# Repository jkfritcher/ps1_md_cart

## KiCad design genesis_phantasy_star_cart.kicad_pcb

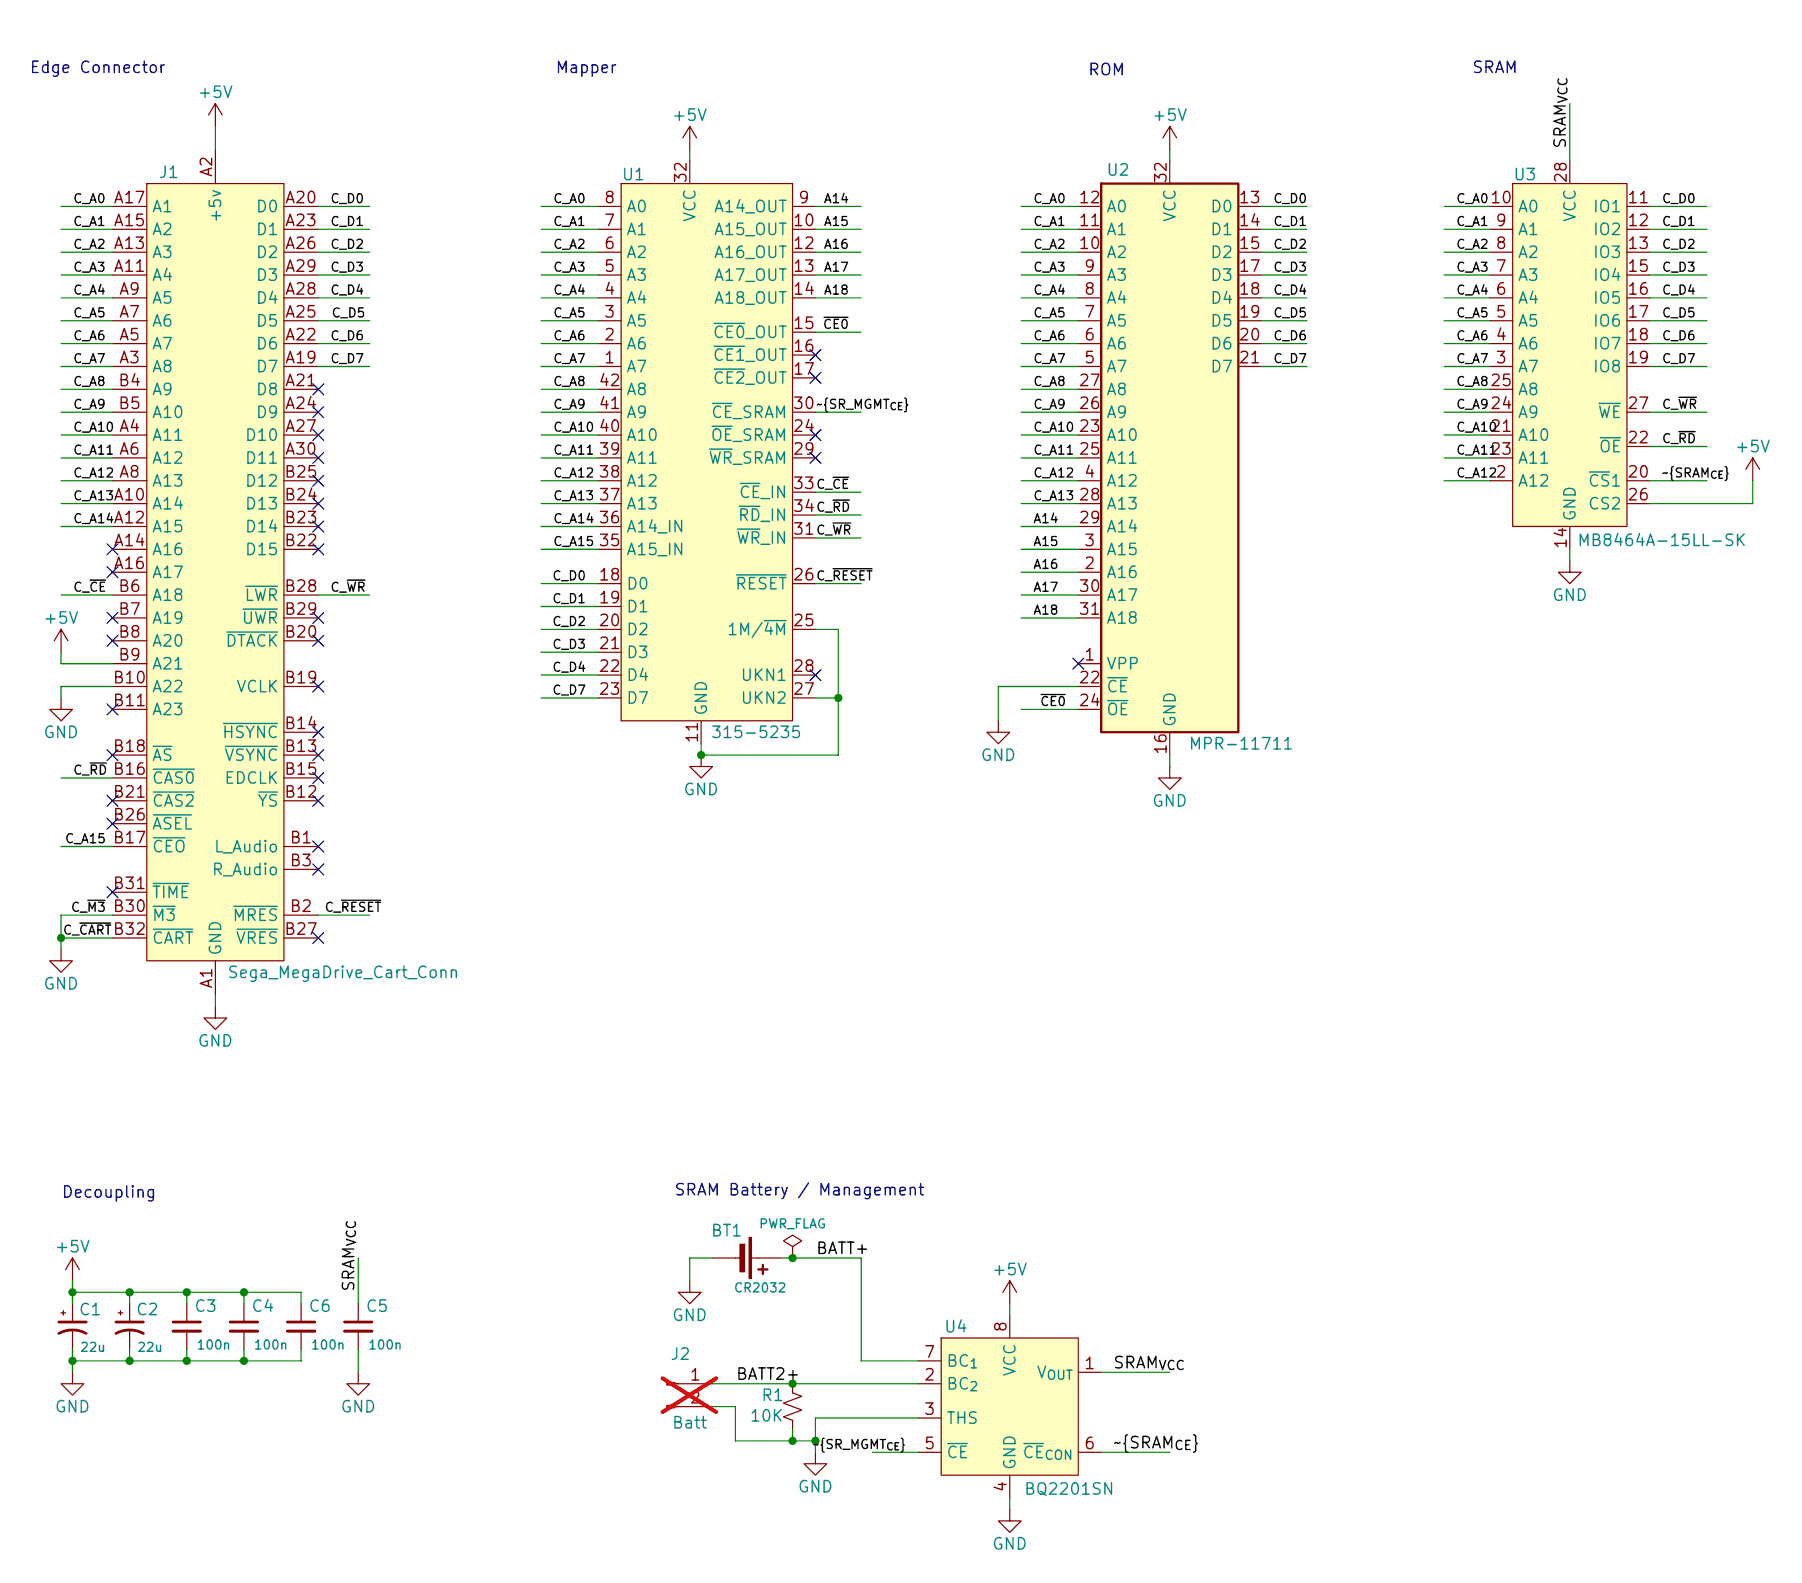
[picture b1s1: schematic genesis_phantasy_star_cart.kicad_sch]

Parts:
BT1: CR2032; CR2032L-F1N
C1, C2: 22u; CP_Elec_4x5.4
C3, C4, C5, C6: 100n; C_0603_1608Metric
J1: Sega_MegaDrive_Cart_Conn; 2x32_P2.54mm_Edge
J2: Batt; PinHeader_1x02_P2.54mm_Vertical; not fitted
R1: 10K; R_0603_1608Metric
U1: 315-5235; SPDIP-42_W15.24mm_P1.78mm
U2: MPR-11711; DIP-32_W15.24mm_LongPads
U3: MB8464A-15LL-SK; DIP-28_W7.62mm_LongPads
U4: BQ2201SN; SOIC-8_3.9x4.9mm_P1.27mm

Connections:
+5V: C1.1, C2.1, C3.1, C4.1, C6.1, J1.A2 (+5v), J1.A31 (+5v), J1.B9 (A21), U1.32 (VCC), U2.32 (VCC), U3.26 (CS2), U4.8 (VCC)
/A14: U1.9 (A14_OUT), U2.29 (A14)
/A15: U1.10 (A15_OUT), U2.3 (A15)
/A16: U1.12 (A16_OUT), U2.2 (A16)
/A17: U1.13 (A17_OUT), U2.30 (A17)
/A18: U1.14 (A18_OUT), U2.31 (A18)
/BATT2+: J2.1, R1.1, U4.2 (BC_{2})
/BATT+: BT1.1 (+), U4.7 (BC_{1})
/C_A0: J1.A17 (A1), U1.8 (A0), U2.12 (A0), U3.10 (A0)
/C_A1: J1.A15 (A2), U1.7 (A1), U2.11 (A1), U3.9 (A1)
/C_A2: J1.A13 (A3), U1.6 (A2), U2.10 (A2), U3.8 (A2)
/C_A3: J1.A11 (A4), U1.5 (A3), U2.9 (A3), U3.7 (A3)
/C_A4: J1.A9 (A5), U1.4 (A4), U2.8 (A4), U3.6 (A4)
/C_A5: J1.A7 (A6), U1.3 (A5), U2.7 (A5), U3.5 (A5)
/C_A6: J1.A5 (A7), U1.2 (A6), U2.6 (A6), U3.4 (A6)
/C_A7: J1.A3 (A8), U1.1 (A7), U2.5 (A7), U3.3 (A7)
/C_A8: J1.B4 (A9), U1.42 (A8), U2.27 (A8), U3.25 (A8)
/C_A9: J1.B5 (A10), U1.41 (A9), U2.26 (A9), U3.24 (A9)
/C_A10: J1.A4 (A11), U1.40 (A10), U2.23 (A10), U3.21 (A10)
/C_A11: J1.A6 (A12), U1.39 (A11), U2.25 (A11), U3.23 (A11)
/C_A12: J1.A8 (A13), U1.38 (A12), U2.4 (A12), U3.2 (A12)
/C_A13: J1.A10 (A14), U1.37 (A13), U2.28 (A13)
/C_A14: J1.A12 (A15), U1.36 (A14_IN)
/C_A15: J1.B17 (~CEO), U1.35 (A15_IN)
/C_D0: J1.A20 (D0), U1.18 (D0), U2.13 (D0), U3.11 (IO1)
/C_D1: J1.A23 (D1), U1.19 (D1), U2.14 (D1), U3.12 (IO2)
/C_D2: J1.A26 (D2), U1.20 (D2), U2.15 (D2), U3.13 (IO3)
/C_D3: J1.A29 (D3), U1.21 (D3), U2.17 (D3), U3.15 (IO4)
/C_D4: J1.A28 (D4), U1.22 (D4), U2.18 (D4), U3.16 (IO5)
/C_D5: J1.A25 (D5), U2.19 (D5), U3.17 (IO6)
/C_D6: J1.A22 (D6), U2.20 (D6), U3.18 (IO7)
/C_D7: J1.A19 (D7), U1.23 (D7), U2.21 (D7), U3.19 (IO8)
/C_~CE: J1.B6 (A18), U1.33 (~CE_IN)
/C_~RD: J1.B16 (~CAS0), U1.34 (~RD_IN), U3.22 (~OE)
/C_~RESET: J1.B2 (~MRES), U1.26 (~RESET)
/C_~WR: J1.B28 (~LWR), U1.31 (~WR_IN), U3.27 (~WE)
/SRAM_{VCC}: C5.1, U3.28 (VCC), U4.1 (V_{OUT})
/~CE0: U1.15 (~CE0_OUT), U2.24 (~OE)
/~SRAM_{CE}: U3.20 (~CS1), U4.6 (~CE_{CON})
/~SR_MGMT_{CE}: U1.30 (~CE_SRAM), U4.5 (~CE)
GND: BT1.2 (-), C1.2, C2.2, C3.2, C4.2, C5.2, C6.2, J1.A1 (GND), J1.A18 (GND), J1.A32 (GND), J1.B10 (A22), J1.B30 (~M3), J1.B32 (~CART), J2.2, R1.2, U1.11 (GND), U1.25 (1M/~4M), U1.27 (UKN2), U2.16 (GND), U2.22 (~CE), U3.14 (GND), U4.3 (THS), U4.4 (GND)

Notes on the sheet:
Decoupling
Mapper
Edge Connector
SRAM
ROM
SRAM Battery / Management

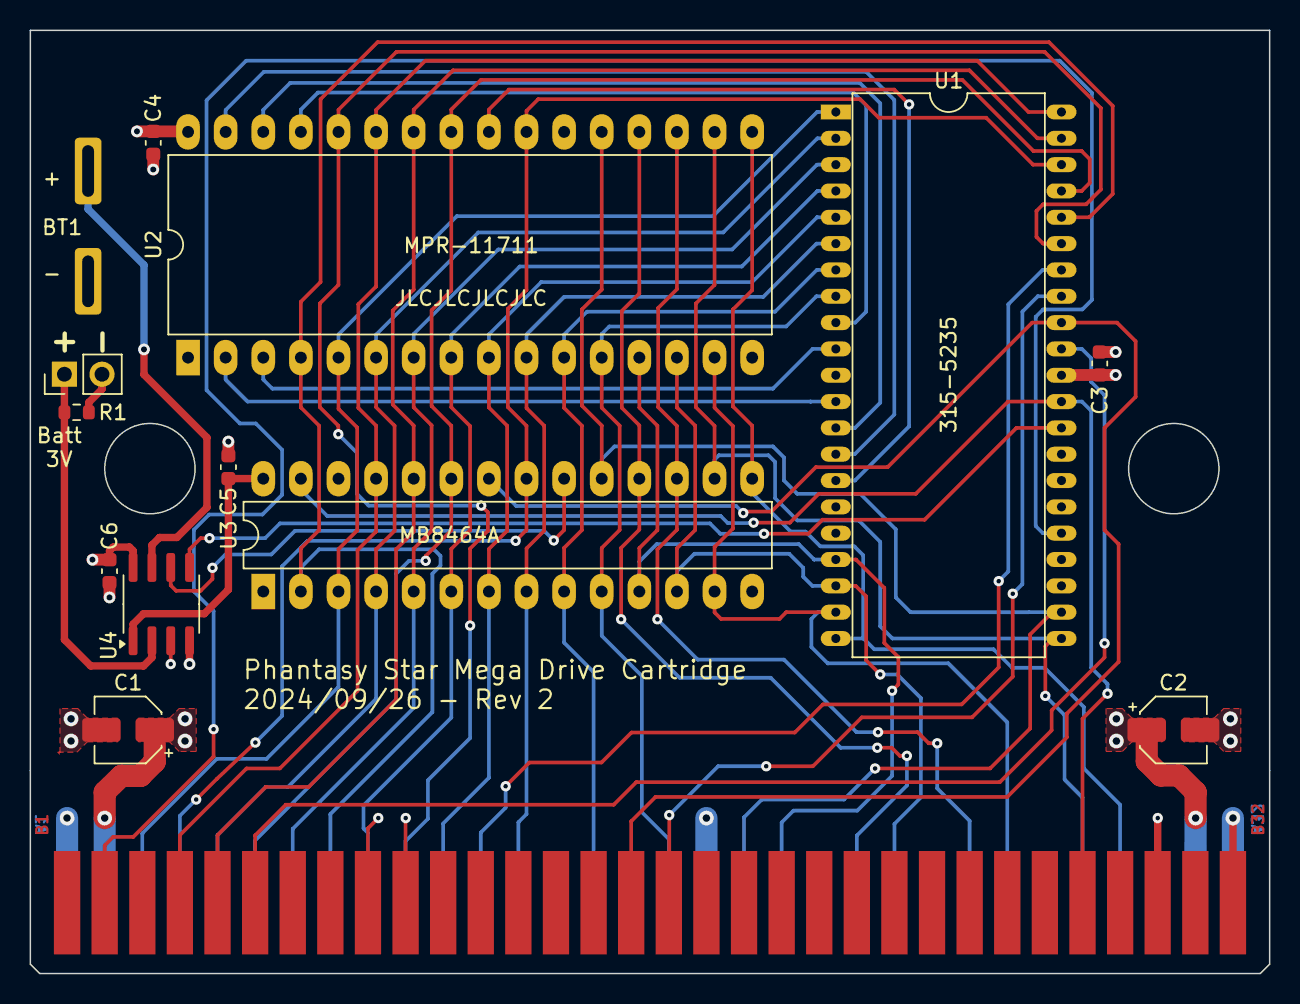
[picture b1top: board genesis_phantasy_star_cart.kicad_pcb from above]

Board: 4 copper layers, 83.7 x 63.7 mm, 14 parts (1 on the bottom side), 41 nets.

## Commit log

2024-07-11 PS1 MD Cartridge Rev 1
    First revision of the Phantasy Star Mega Drive cartridge. This rev has
    been sent for printing to test the basic functionality before final
    design work is complete.
    Following changes are still needed before being complete.
    * Layout and footprint for CR2032 is needed. Currently has 2 pin headers
    to attach a battery for testing.
2024-07-18 Add 3d model for mapper
    * Added 3D model for the U1 mapper chip
    * Added an extra +5v and GND via to C1 and C2.
2024-07-18 Rename mapper footprint and model
    * Renamed footprint and model for mapper to be more accurate and with
    the dimentions in metric.
2024-07-19 Updated .gitignore
2024-09-22 Changes leading to Rev 2 of the board
    * Trimmed wings off of the edges of the board to make it a regular
    shape.
    * Slightly moved around U1/2/3 to make more room around the cutouts.
    * Moved backup battery connection, but remains pin headers as a CR2032
    footprint won't fit on the board with the ICs where they are.
    * Enlarged drill size for U1 pads to allow the pins to fit easier.
2024-09-25 Add NPTH for potential use by battery wires
    * Added NPTH for battery wires to use for front soldering. Possible
    stress relief for the wires.
    * Rotated battery pin headers to orient better with NPTH.
2024-09-26 Convert backup battery to proper footprint
    * Backup battery is now using a proper footprint for a CR2032 with
    solder tabs. Kapton tape will be needed between battery and pins on
    the backside of the board.
    * Converted battery pin header to be a secondary battery to
    maintain the SRAM while changing the primary battery. Added a pulldown
    to this to keep the supervisor happy while the seconary is not
